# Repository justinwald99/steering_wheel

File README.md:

# Steering-Wheel

## Setup

The CAN board used by the steering wheel needs to be setup before it can be used in the Python code for the wheel.

**Step 1:** &nbsp;Add the CAN device to the /boot/config.txt folder on the Pi. To do this, run vim (not installed by default) on the config.txt file with sudo by running the following command:  

    sudo vim /boot/config.txt
and add the following lines:  

    dtoverlay=spi1-3cs
    dtoverlay=mcp2515-can1-1,oscillator=16000000,interrupt=12
The line `dtoverlay=spi1-3cs` tells the raspberry Pi to enable the second spi bus, which is spi1.0, spi1.1, and spi1.2 (the .0, .1, and .2 indicate which chip select a device is using and is allowed reffered to as CS or CE). We need to use the second spi bus because the first one (spi0.0 and spi0.1) is being used by the screen.  
The next line, `dtoverlay=mcp2515-can1-1,oscillator=16000000,interrupt=12` is where we register our CAN chip. This is done by loading the `mcp2515-can1-1` overlay and passing it parameters for the oscillator and interrupt. This overlay will have to be downloaded from this repo (in the Pi `Overlays/Compiled` folder) because the default linux overlays for the MCP2515 only work for spi 0.0 and 0.1. Typically, the 1-1 version should be used, which is written for spi1.1 (CS on BCM pin 17), but I've also created and compiled overlays for 1.0 and 1.2 in case those pins are more convenient. The parameters should be pretty simple, the oscillator is the frequency of the crystal oscillator hooked to the mcp2515 and the interrupt is the pin wired to the interrupt of the MCP2515.  
If done correctly, an entry named **can0** should appear when running the `ifconfig -a` command.

**Step 2:**&nbsp; Automatically start the can network on system start. You can manually start the can0 network with the `sudo ip link set can0 up type can bitrate 1000000` command. Ideally, however, we want this network to be created on startup. This is achieved by adding the following code to the `/etc/network/interfaces` file:

    auto can0
    iface can0 inet manual
        pre-up ip link set $IFACE type can bitrate 1000000 listen-only off restart-ms 1
        up /sbin/ifconfig $IFACE up
        down /sbin/ifconfig $IFACE down
If successful, the command `candump can0` shouldn't produce an error and should provide a stream of can messages being received by the board.  
**Step 3:**&nbsp; Setup the screen. To do this, paste the following commands into the Pi's terminal:

    cd ~
    wget https://raw.githubusercontent.com/adafruit/Raspberry-Pi-Installer-Scripts/master/adafruit-pitft.sh
    chmod +x adafruit-pitft.sh
    sudo ./adafruit-pitft.sh
This will run Adafruit's automated setup procedure. Fill out the options for the 3.5in resistive screen and rotate it 90 degrees. Then answer "no" to the question `Would you like the console to appear on the PiTFT display` and yes to the question `Would you like the HDMI display to mirror to the PiTFT display?`. For more information about this process follow the guide at  https://learn.adafruit.com/adafruit-pitft-3-dot-5-touch-screen-for-raspberry-pi/easy-install-2.

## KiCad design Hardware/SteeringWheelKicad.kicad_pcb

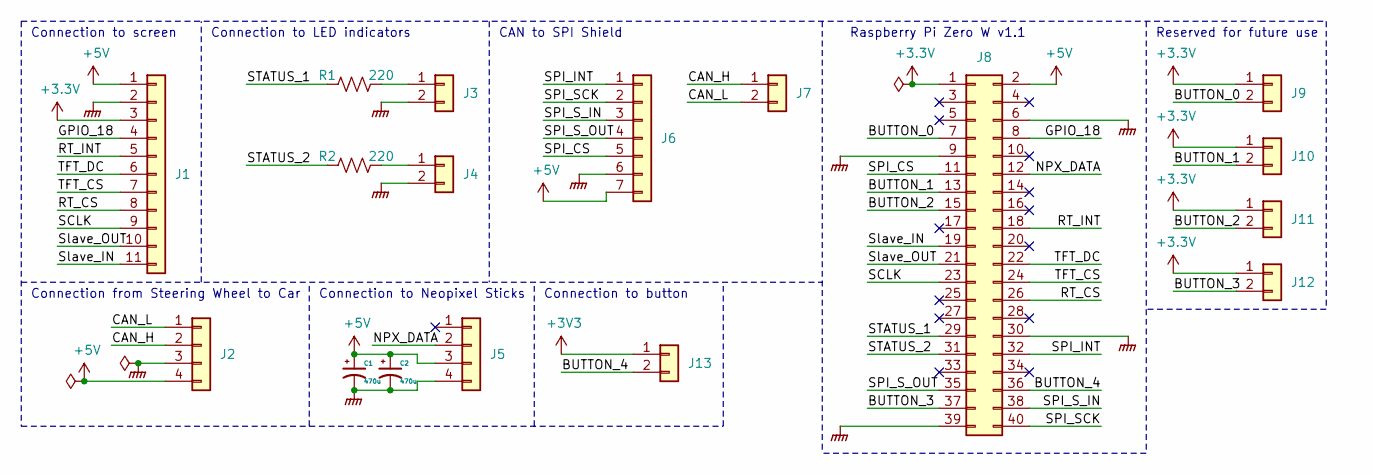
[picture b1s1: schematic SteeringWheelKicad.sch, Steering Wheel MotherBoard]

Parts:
C1, C2: 470u; CAPPM7343X310N
J1: Conn_01x11; PinHeader_1x11_P2.54mm_Vertical
J2, J5: Conn_01x04; PinHeader_1x04_P2.54mm_Vertical
J3, J4, J7, J9, J10, J11, J12, J13: Conn_01x02; PinHeader_1x02_P2.54mm_Vertical
J6: Conn_01x07; PinHeader_1x07_P2.54mm_Vertical
J8: Conn_02x20_Odd_Even; PinHeader_2x20_P2.54mm_Vertical
R1, R2: 220; R_Axial_DIN0207_L6.3mm_D2.5mm_P10.16mm_Horizontal

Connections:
+5V: C1.1, C2.1, J1.1, J2.4, J5.3, J6.7, J8.2
/BUTTON_0: J8.7, J9.2
/BUTTON_1: J8.13, J10.2
/BUTTON_2: J8.15, J11.2
/BUTTON_3: J8.37, J12.2
/BUTTON_4: J8.36, J13.2
/CAN_H: J2.2, J7.1
/CAN_L: J2.1, J7.2
/GPIO_18: J1.4, J8.8
/NPX_DATA: J5.2, J8.12
/RT_CS: J1.8, J8.26
/RT_INT: J1.5, J8.18
/SCLK: J1.9, J8.23
/SPI_CS: J6.5, J8.11
/SPI_INT: J6.1, J8.32
/SPI_SCK: J6.2, J8.40
/SPI_S_IN: J6.3, J8.38
/SPI_S_OUT: J6.4, J8.35
/STATUS_1: J8.29, R1.2
/STATUS_2: J8.31, R2.2
/Slave_IN: J1.11, J8.19
/Slave_OUT: J1.10, J8.21
/TFT_CS: J1.7, J8.24
/TFT_DC: J1.6, J8.22
GNDPWR: C1.2, C2.2, J1.2, J2.3, J3.2, J4.2, J5.4, J6.6, J8.6, J8.9, J8.30, J8.39
unnamed: J3.1, R1.1
unnamed: J4.1, R2.1

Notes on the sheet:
Connection to screen
Connection to LED indicators
CAN to SPI Shield
Connection to Neopixel Sticks
Connection from Steering Wheel to Car
Connection to button
Reserved for future use
Raspberry Pi Zero W v1.1

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
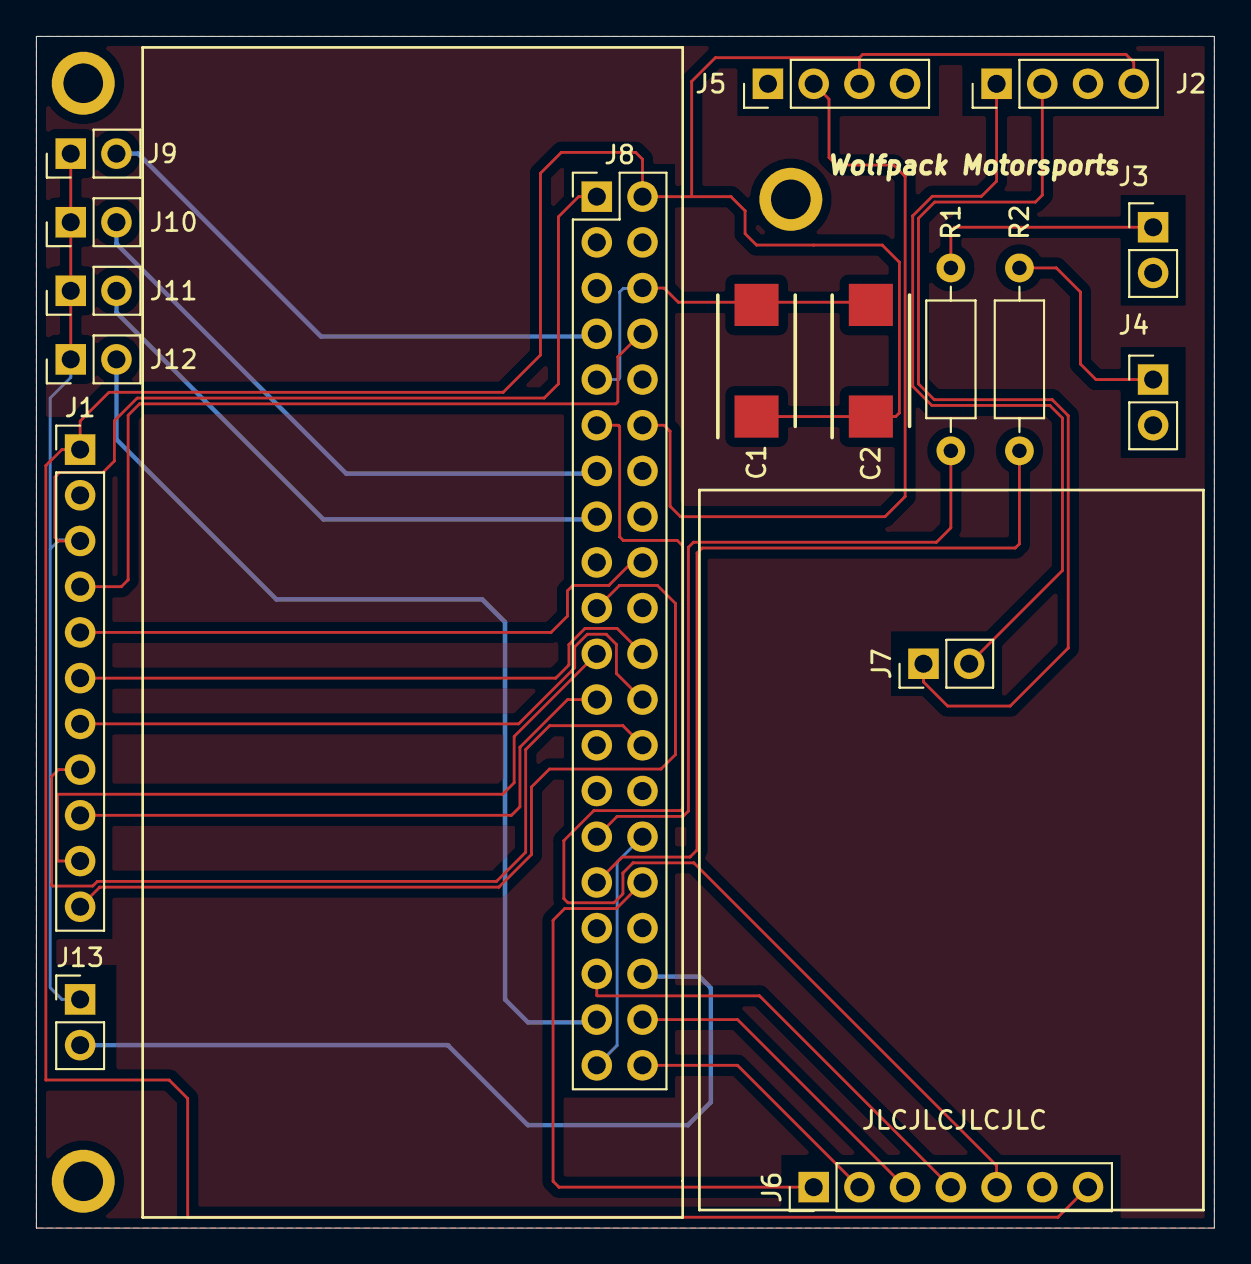
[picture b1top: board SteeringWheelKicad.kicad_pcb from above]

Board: 2 copper layers, 65.4 x 66.2 mm, 20 parts (0 on the bottom side), 28 nets.

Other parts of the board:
MH1, MH2, MH3: MountingHole_2.2mm_M2_ISO7380_Pad

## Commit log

2019-11-11 Added documentation for the CAN board setup on the Pi.
2019-11-11 Reorganized files
2019-11-11 Added instructions for screen setup.
2019-11-17 Initial implementation of CAN reading.
2020-01-16 worked on ui
2020-01-16 Partial change to ui
2020-01-16 small commit
2020-01-23 Big progress on screen
2020-01-23 Completed voltage, gearpos, and gauges.
2020-05-07 Updated comments for ui classes
2020-05-12 Added RPM gauge.
2020-05-12 Partial rework
2020-06-03 Began rework
2020-06-05 Working rework pre-warning
2020-06-11 pre-yaml rework
2020-06-11 Implemeneted yaml config. [testing]
2020-06-11 small tweaks from pi
2020-06-13 added background animation
2020-06-19 Added schematics folder
2020-06-19 Added support for conditional based warnings. Added logtofile capability.
2020-06-19 Removed demo code.
2020-06-19 Added quick comment.
2020-06-19 Added name of can channel under warning.
2020-06-19 WIP of theme support
2020-06-22 Added central theme object to update ui_elements.
2020-06-22 removed old files
2020-06-22 Disabled the wolf background in darkmode.
2020-06-22 Reorganized theme information
2020-06-23 Added documentation.
2020-06-23 Began implementation of physical button interaction.
2020-06-23 fixed screen dimming
2020-06-23 Added support for the two status LEDs.
2020-06-24 Updated screen backlight control pin.
2020-06-24 Added shiftlight support.
2020-06-28 Create foo.txt
    "Changing the folder name" of schematics to Hardware to better reflect what it contains
2020-06-28 Add files via upload
    The current version of the steering wheel
2020-06-28 Deleting placeholder
2020-06-28 uploaded gerbers
2020-06-28 Drill maps added
    Drill maps are not necessary normally but it is here just in case we need it
2020-06-28 Add files via upload
    erc and drc reports as well as export reports
2020-06-28 Add files via upload
    Not sure if the project uses this but it is here if we need it
2020-06-28 Upload of project complete
    Removed remaining place holders. Dev_Legacy is avaible in the archived zip file.
2020-12-16 unknown changes
2020-12-23 back to avl changes
2021-01-12 Refactored code to use config files.
2021-01-14 Finished refactor and reorg.
